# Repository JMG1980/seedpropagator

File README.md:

# seedpropagator
Arduino Seed Propagator
## Description
- Environmental box for controlling temperature, lighting, ventilation and irrigation. Data displayed on LCD and saved locally in SD card. 
- Conceived to extend the growing season at the allotment and to experiment with indoor growing.

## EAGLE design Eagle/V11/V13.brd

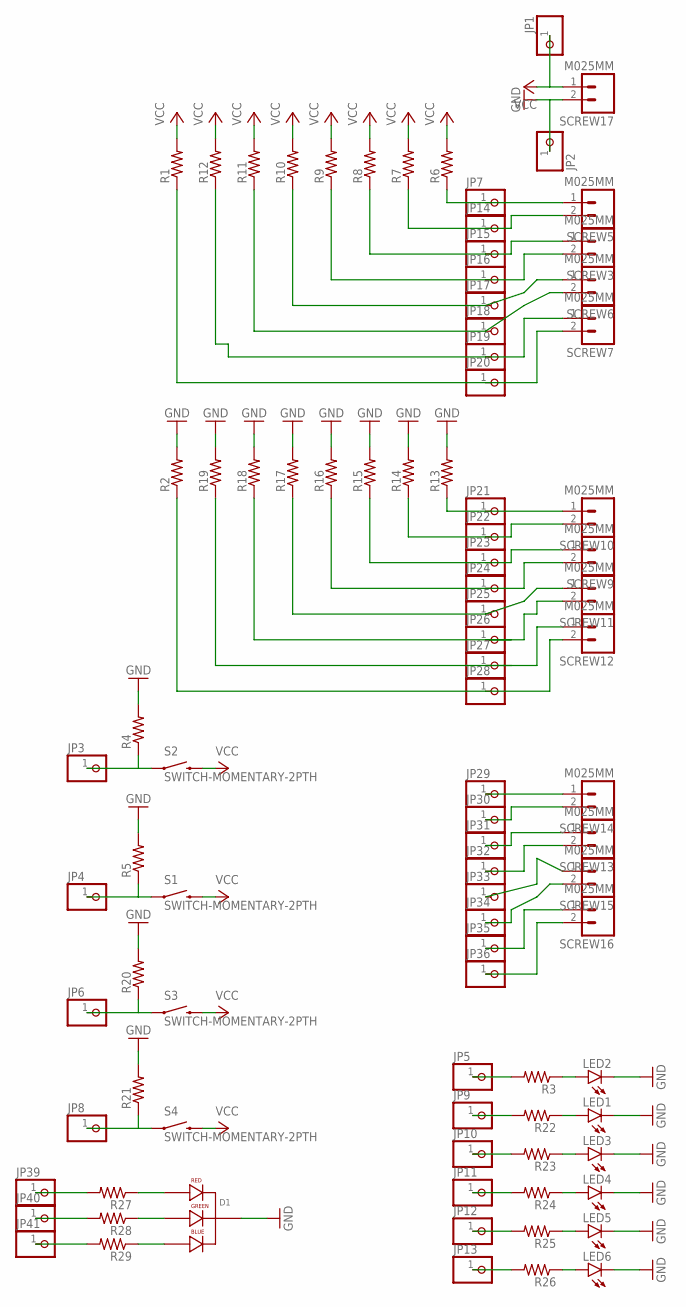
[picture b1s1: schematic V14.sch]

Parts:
D1: LED-RGB-CC-THRUCLEAR; LED-RGB-THRU
JP1, JP2, JP3, JP4, JP5, JP6, JP7, JP8, JP9, JP10, JP11, JP12, JP13, JP14, JP15, JP16, JP17, JP18, JP19, JP20, JP21, JP22, JP23, JP24, JP25, JP26, JP27, JP28, JP29, JP30, JP31, JP32, JP33, JP34, JP35, JP36, JP39, JP40, JP41: PINHD-1X1; 1X01
LED1, LED2, LED3, LED4, LED5, LED6: LED-3MM-NO_SILK; LED3MM-NS
R1, R2, R3, R4, R5, R6, R7, R8, R9, R10, R11, R12, R13, R14, R15, R16, R17, R18, R19, R20, R21, R22, R23, R24, R25, R26, R27, R28, R29: R-US_0207/9; 0207/9
S1, S2, S3, S4: SWITCH-MOMENTARY-2PTH; TACTILE-PTH
SCREW3, SCREW5, SCREW6, SCREW7, SCREW9, SCREW10, SCREW11, SCREW12, SCREW13, SCREW14, SCREW15, SCREW16, SCREW17: M025MM; SCREWTERMINAL-5MM-2

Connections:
GND: D1.2 (CATHODE), JP2.1, LED1.K (C), LED2.K (C), LED3.K (C), LED4.K (C), LED5.K (C), LED6.K (C), R2.2, R4.2, R5.2, R13.2, R14.2, R15.2, R16.2, R17.2, R18.2, R19.2, R20.2, R21.2, SCREW17.2
unnamed: JP3.1, R4.1, S2.1
unnamed: JP29.1, SCREW14.1
unnamed: JP20.1, R1.1, SCREW7.2
unnamed: LED2.A, R3.1
unnamed: JP5.1, R3.2
unnamed: JP4.1, R5.1, S1.1
unnamed: JP17.1, R10.1, SCREW6.1
unnamed: JP18.1, R11.1, SCREW6.2
unnamed: JP19.1, R12.1, SCREW7.1
unnamed: JP7.1, R6.1, SCREW5.1
unnamed: JP14.1, R7.1, SCREW5.2
unnamed: JP15.1, R8.1, SCREW3.1
unnamed: JP16.1, R9.1, SCREW3.2
unnamed: JP21.1, R13.1, SCREW10.1
unnamed: JP22.1, R14.1, SCREW10.2
unnamed: JP23.1, R15.1, SCREW9.1
unnamed: JP24.1, R16.1, SCREW9.2
unnamed: JP25.1, R17.1, SCREW11.1
unnamed: JP6.1, R20.1, S3.1
unnamed: JP27.1, R19.1, SCREW12.1
unnamed: JP34.1, SCREW15.2
unnamed: JP35.1, SCREW16.1
unnamed: JP36.1, SCREW16.2
unnamed: JP26.1, R18.1, SCREW11.2
unnamed: JP28.1, R2.1, SCREW12.2
unnamed: JP8.1, R21.1, S4.1
unnamed: LED1.A, R22.1
unnamed: JP9.1, R22.2
unnamed: JP30.1, SCREW14.2
unnamed: JP31.1, SCREW13.1
unnamed: JP32.1, SCREW13.2
unnamed: JP33.1, SCREW15.1
unnamed: LED3.A, R23.1
unnamed: JP10.1, R23.2
unnamed: LED4.A, R24.1
unnamed: JP11.1, R24.2
unnamed: LED5.A, R25.1
unnamed: JP12.1, R25.2
unnamed: LED6.A, R26.1
unnamed: JP13.1, R26.2
unnamed: D1.1 (RED_CATHODE), R27.1
unnamed: D1.3 (GREEN_CATHODE), R28.1
unnamed: D1.4 (BLUE_CATHODE), R29.1
unnamed: JP39.1, R27.2
unnamed: JP40.1, R28.2
unnamed: JP41.1, R29.2
VCC: JP1.1, R1.2, R6.2, R7.2, R8.2, R9.2, R10.2, R11.2, R12.2, S1.3 (2), S2.3 (2), S3.3 (2), S4.3 (2), SCREW17.1

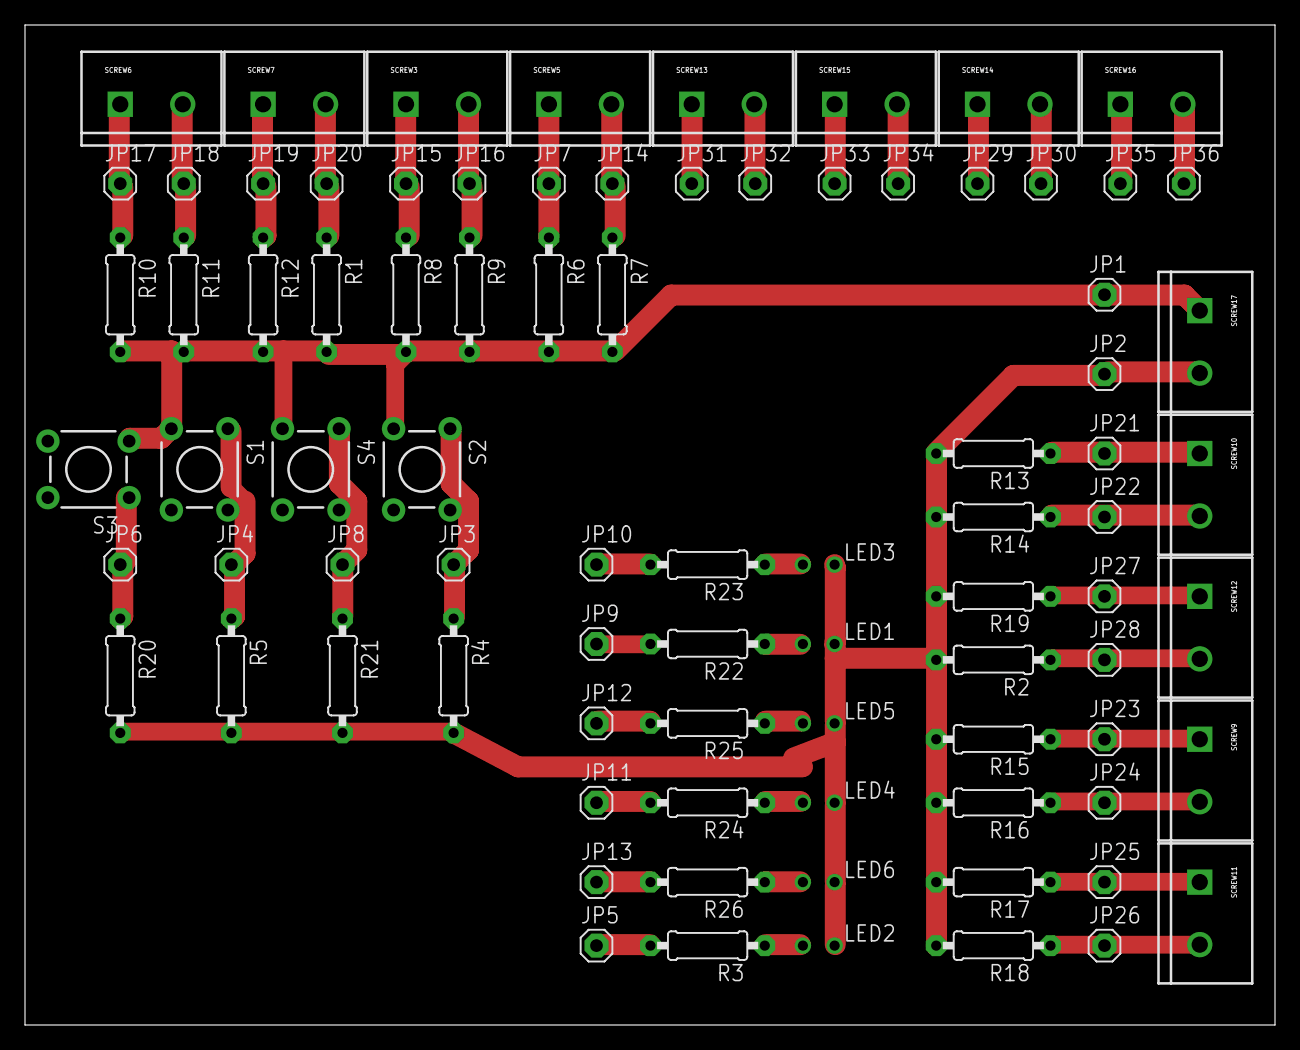
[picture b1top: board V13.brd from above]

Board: 2 copper layers, 100.0 x 80.0 mm, 85 parts (0 on the bottom side), 42 nets.

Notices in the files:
parts and their libraries:
SparkFun-Connectors: Licensing: Creative Commons ShareAlike 4.0 International - https://creativecommons.org/licenses/by-sa/4.0
